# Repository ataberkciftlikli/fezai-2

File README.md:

# fezai-2
Halley'in Çırakları Rocket Team - Fezai II - Flight Computer - 2021

Main Flight Computer -> Teensy 3.5 Microcontroller
                     -> Adafruit Ultimate GPS
                     -> Xbee Pro S2C
                     -> BMP 280
                     -> MPU6050
                     -> LM2596-ADJ
                     -> IRF540

Second Flight Computer -> Teensy 3.5 Microcontroller
                       -> Adafruit Ultimate GPS
                       -> Xbee Pro S2C
                       -> BMP 180
                       -> MPU9050
                       -> LM2596-ADJ
                       -> IRF540

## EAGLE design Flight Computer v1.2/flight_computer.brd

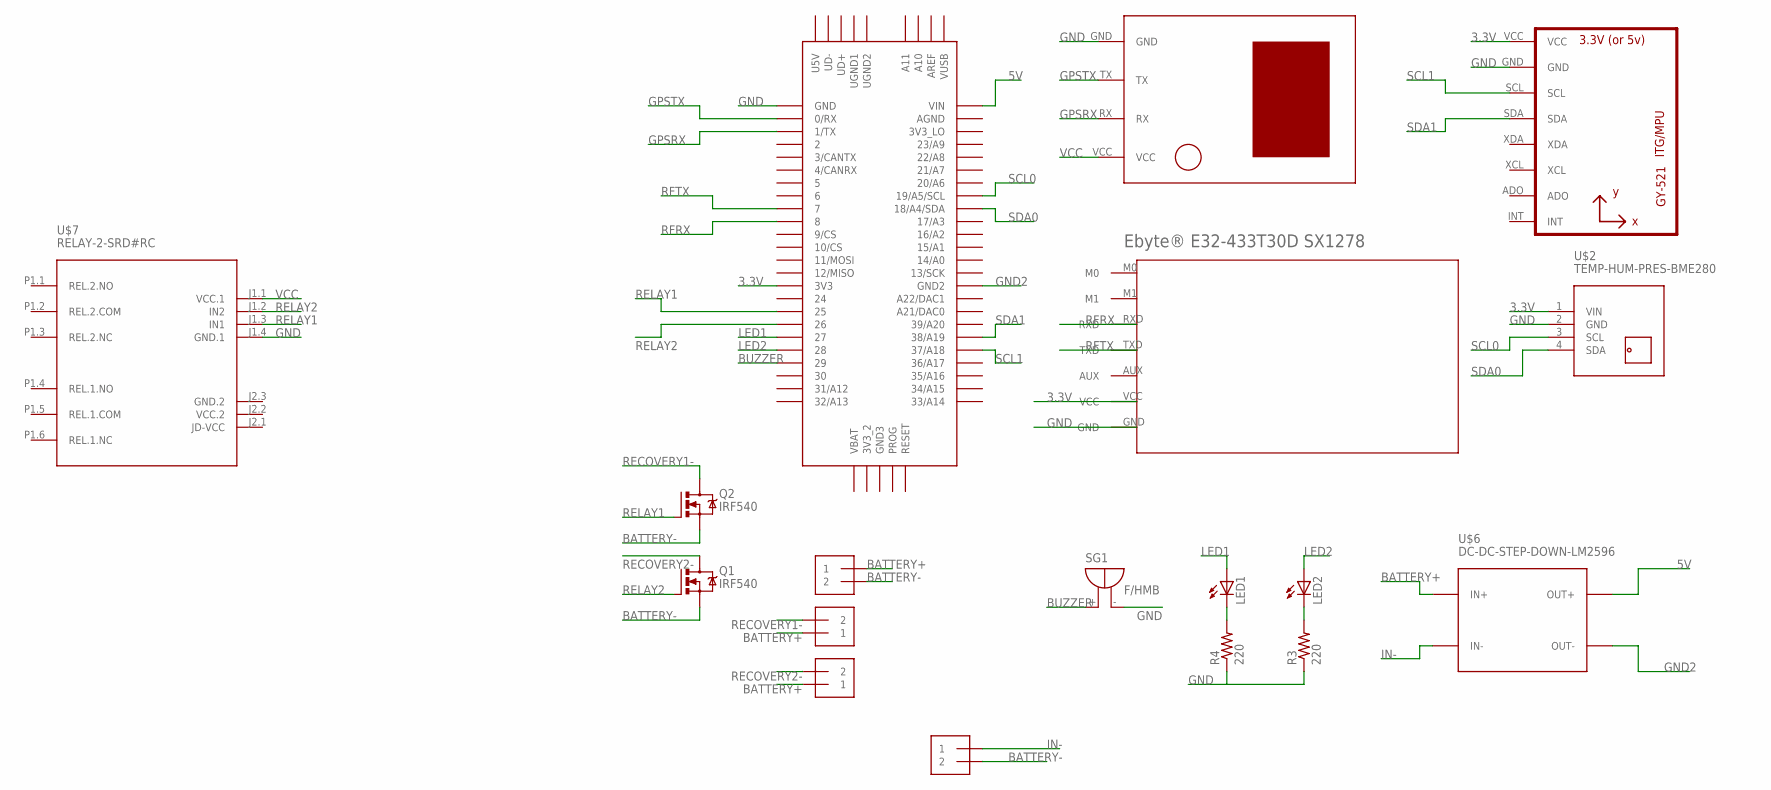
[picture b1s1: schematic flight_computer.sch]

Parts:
J1, J2, J3, J4: 1X2-3.5MM
LED1, LED2: LED5MM
Q1, Q2: IRF540; TO220BV
R3, R4: 220; 0204/7
SG1: F/HMB
U1: GY-521MPU6050; GY-521
U$1: U-BLOX-NEO6V2
U$2: TEMP-HUM-PRES-BME280
U$3: TEENSY_3.5/3.6
U$4: EBYTE®E32-433T30DSX1278; E32-433T30D
U$6: DC-DC-STEP-DOWN-LM2596
U$7: RELAY-2-SRD#RC

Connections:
3.3V: U1.VCC, U$2.1 (VIN), U$3.3V3, U$4.VCC
5V: U$3.VIN, U$6.OUT+
BATTERY+: J1.1, J2.1, J3.1, U$6.IN+
BATTERY-: J1.2, J4.2, Q1.S, Q2.S
BUZZER: SG1.+, U$3.29
GND: R3.1, R4.1, SG1.-, U1.GND, U$1.GND, U$2.2 (GND), U$3.GND, U$4.GND, U$7.J1.4 (GND.1)
GND2: U$3.GND2, U$6.OUT-
GND.2: U$7.J2.3 (GND.2)
GPSRX: U$1.RX, U$3.1/TX
GPSTX: U$1.TX, U$3.0/RX
IN-: J4.1, U$6.IN-
LED1: LED1.A, U$3.27
LED2: LED2.A, U$3.28
unnamed: LED1.K (C), R4.2
unnamed: LED2.K (C), R3.2
RECOVERY1-: J2.2, Q2.D
RECOVERY2-: J3.2, Q1.D
RELAY1: Q2.G, U$3.25, U$7.J1.3 (IN1)
RELAY2: Q1.G, U$3.26, U$7.J1.2 (IN2)
RFRX: U$3.8, U$4.RXD
RFTX: U$3.7, U$4.TXD
SCL0: U$2.3 (SCL), U$3.19/A5/SCL
SCL1: U1.SCL, U$3.37/A18
SDA0: U$2.4 (SDA), U$3.18/A4/SDA
SDA1: U1.SDA, U$3.38/A19
VCC: U$1.VCC, U$7.J1.1 (VCC.1)
VCC.2: U$7.J2.2 (VCC.2)

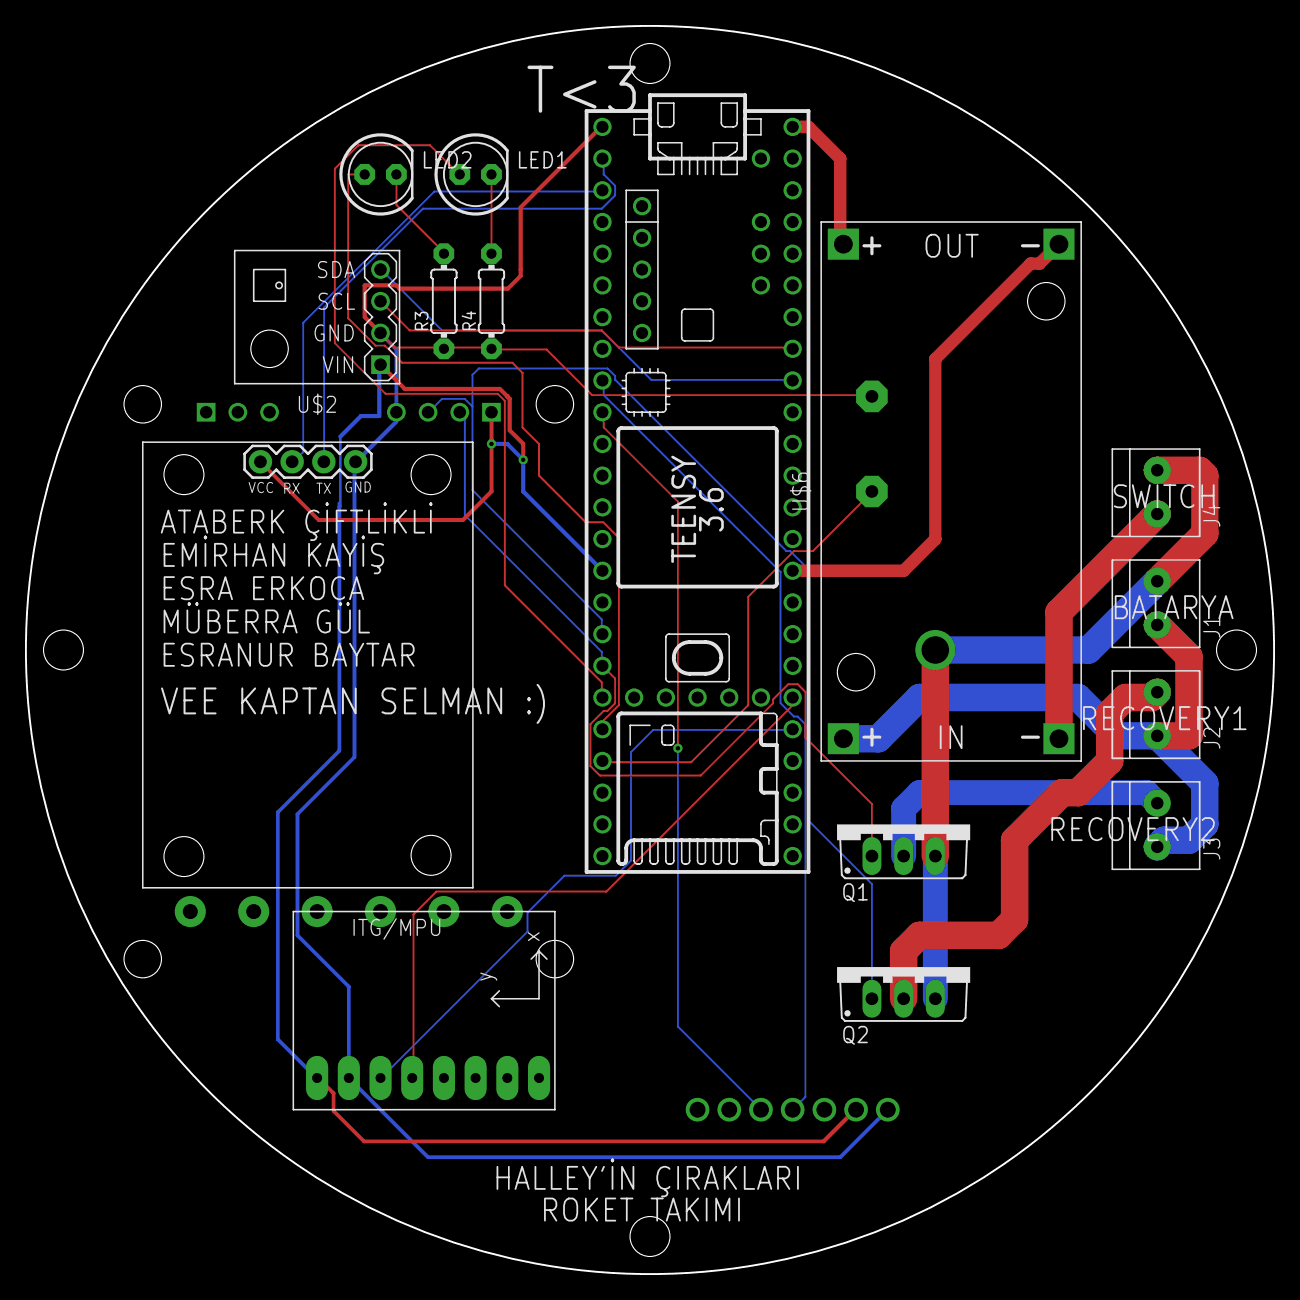
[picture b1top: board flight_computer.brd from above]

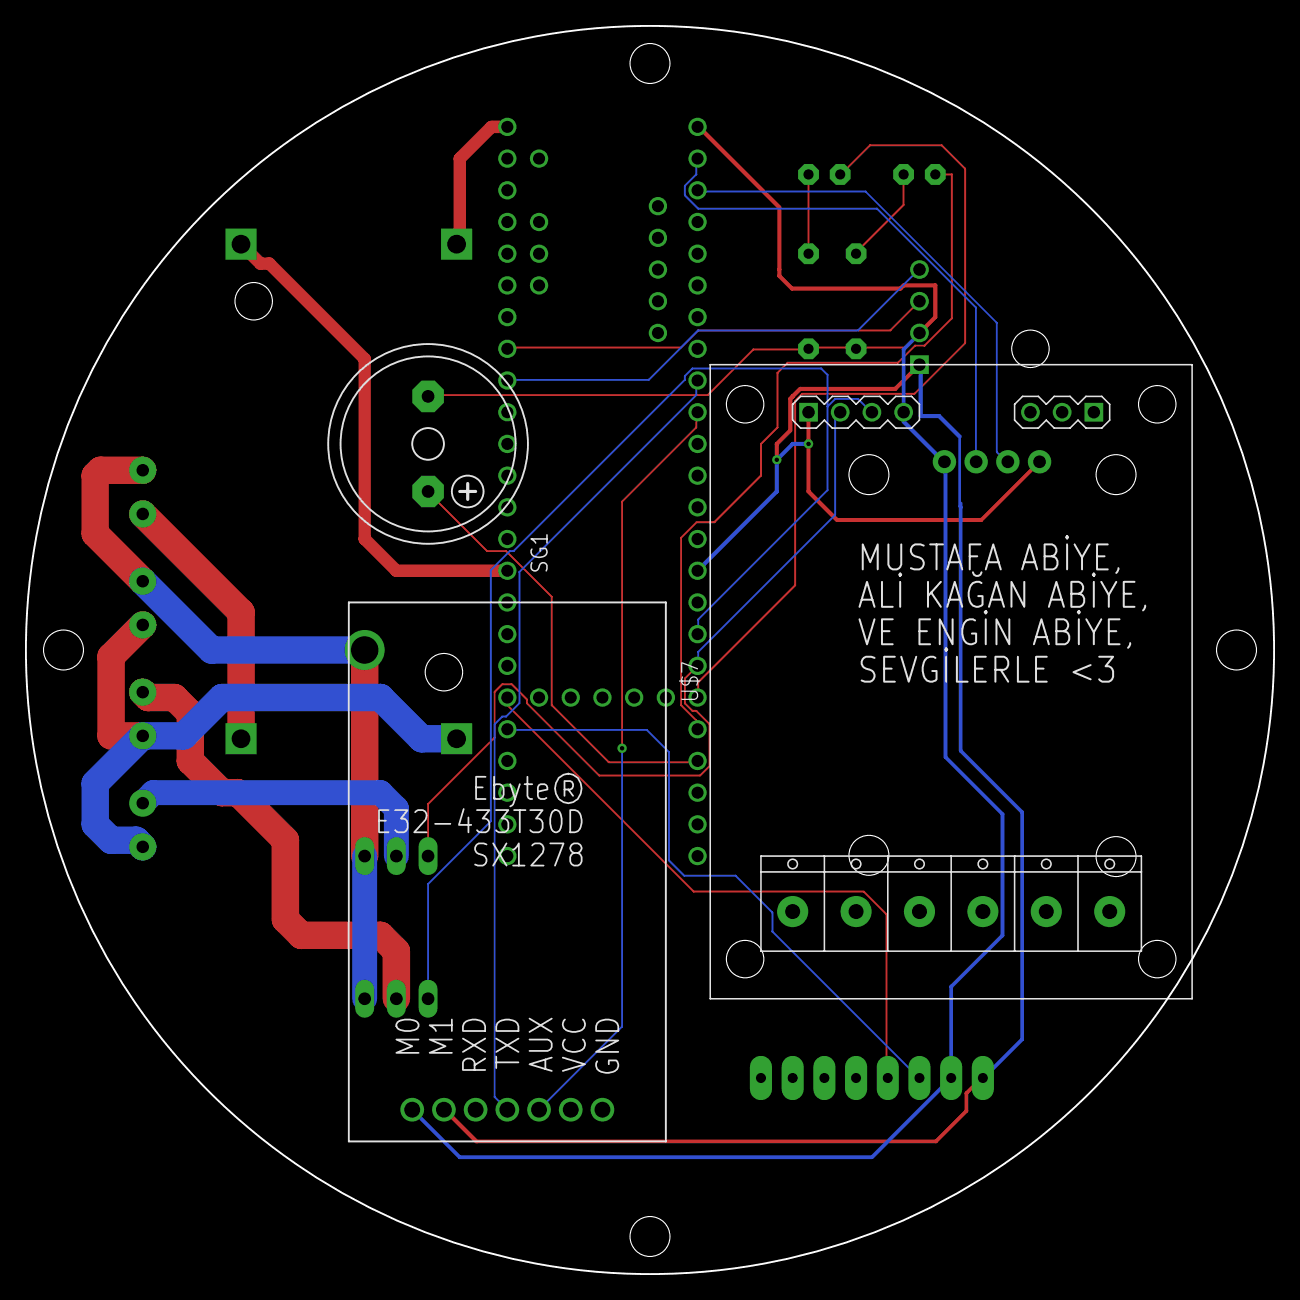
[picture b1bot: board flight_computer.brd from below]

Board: 2 copper layers, 100.0 x 100.0 mm, 18 parts (3 on the bottom side), 25 nets.

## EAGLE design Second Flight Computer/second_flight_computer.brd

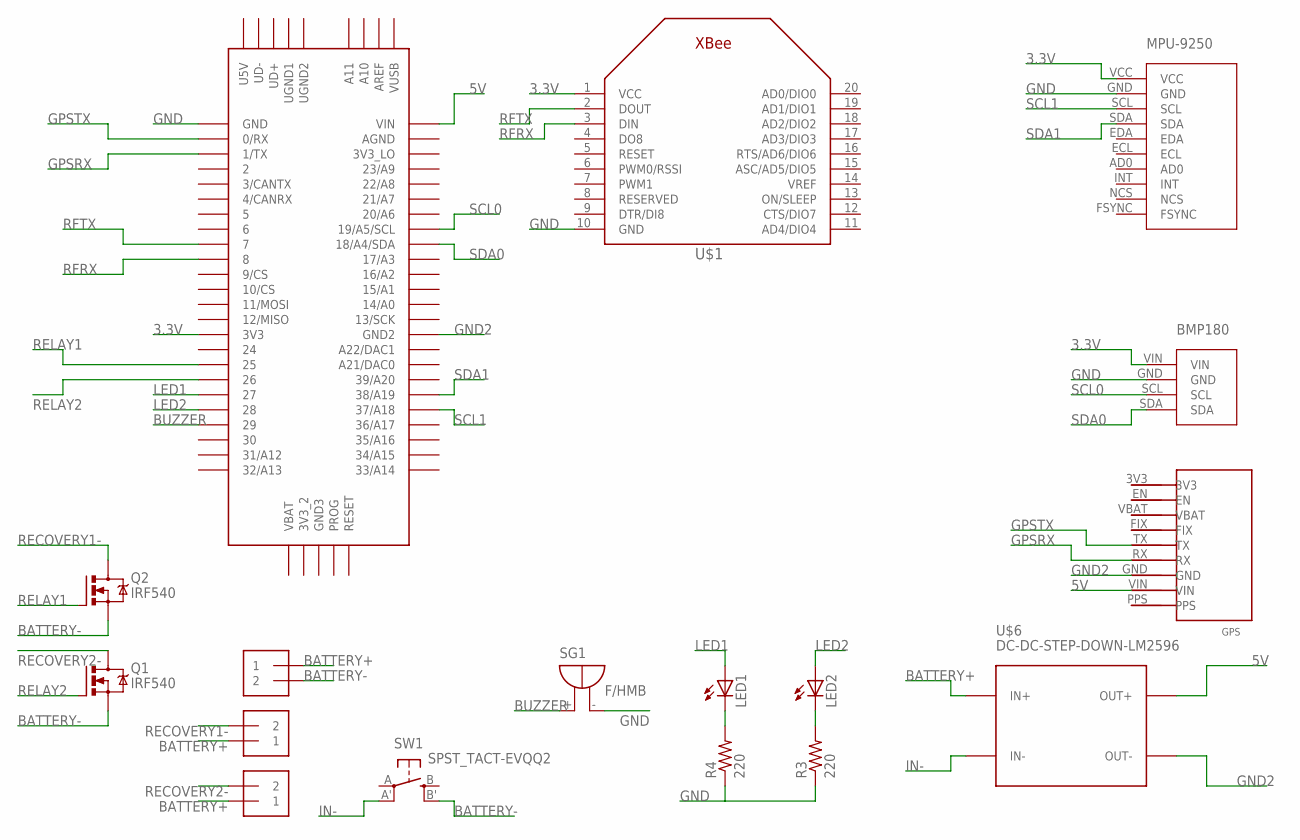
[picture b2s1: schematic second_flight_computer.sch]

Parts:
BMP1: BMP180
J1, J2, J3: 1X2-3.5MM
LED1, LED2: LED5MM
MPU-1: MPU-9250
Q1, Q2: IRF540; TO220BV
R3, R4: 220; 0204/7
SG1: F/HMB
SW1: SPST_TACT-EVQQ2; EVQ-Q2
U$1: XBEE
U$3: TEENSY_3.5/3.6
U$5: GPS
U$6: DC-DC-STEP-DOWN-LM2596

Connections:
3.3V: BMP1.VIN, MPU-1.VCC, U$1.1 (VCC), U$3.3V3
5V: U$3.VIN, U$5.VIN, U$6.OUT+
BATTERY+: J1.1, J2.1, J3.1, U$6.IN+
BATTERY-: J1.2, Q1.S, Q2.S, SW1.B' (S1)
BUZZER: SG1.+, U$3.29
GND: BMP1.GND, MPU-1.GND, R3.1, R4.1, SG1.-, U$1.10 (GND), U$3.GND
GND2: U$3.GND2, U$5.GND, U$6.OUT-
GPSRX: U$3.1/TX, U$5.RX
GPSTX: U$3.0/RX, U$5.TX
IN-: SW1.A' (P1), U$6.IN-
LED1: LED1.A, U$3.27
LED2: LED2.A, U$3.28
unnamed: LED1.K (C), R4.2
unnamed: LED2.K (C), R3.2
RECOVERY1-: J2.2, Q2.D
RECOVERY2-: J3.2, Q1.D
RELAY1: Q2.G, U$3.25
RELAY2: Q1.G, U$3.26
RFRX: U$1.3 (DIN), U$3.8
RFTX: U$1.2 (DOUT), U$3.7
SCL0: BMP1.SCL, U$3.19/A5/SCL
SCL1: MPU-1.SCL, U$3.37/A18
SDA0: BMP1.SDA, U$3.18/A4/SDA
SDA1: MPU-1.SDA, U$3.38/A19

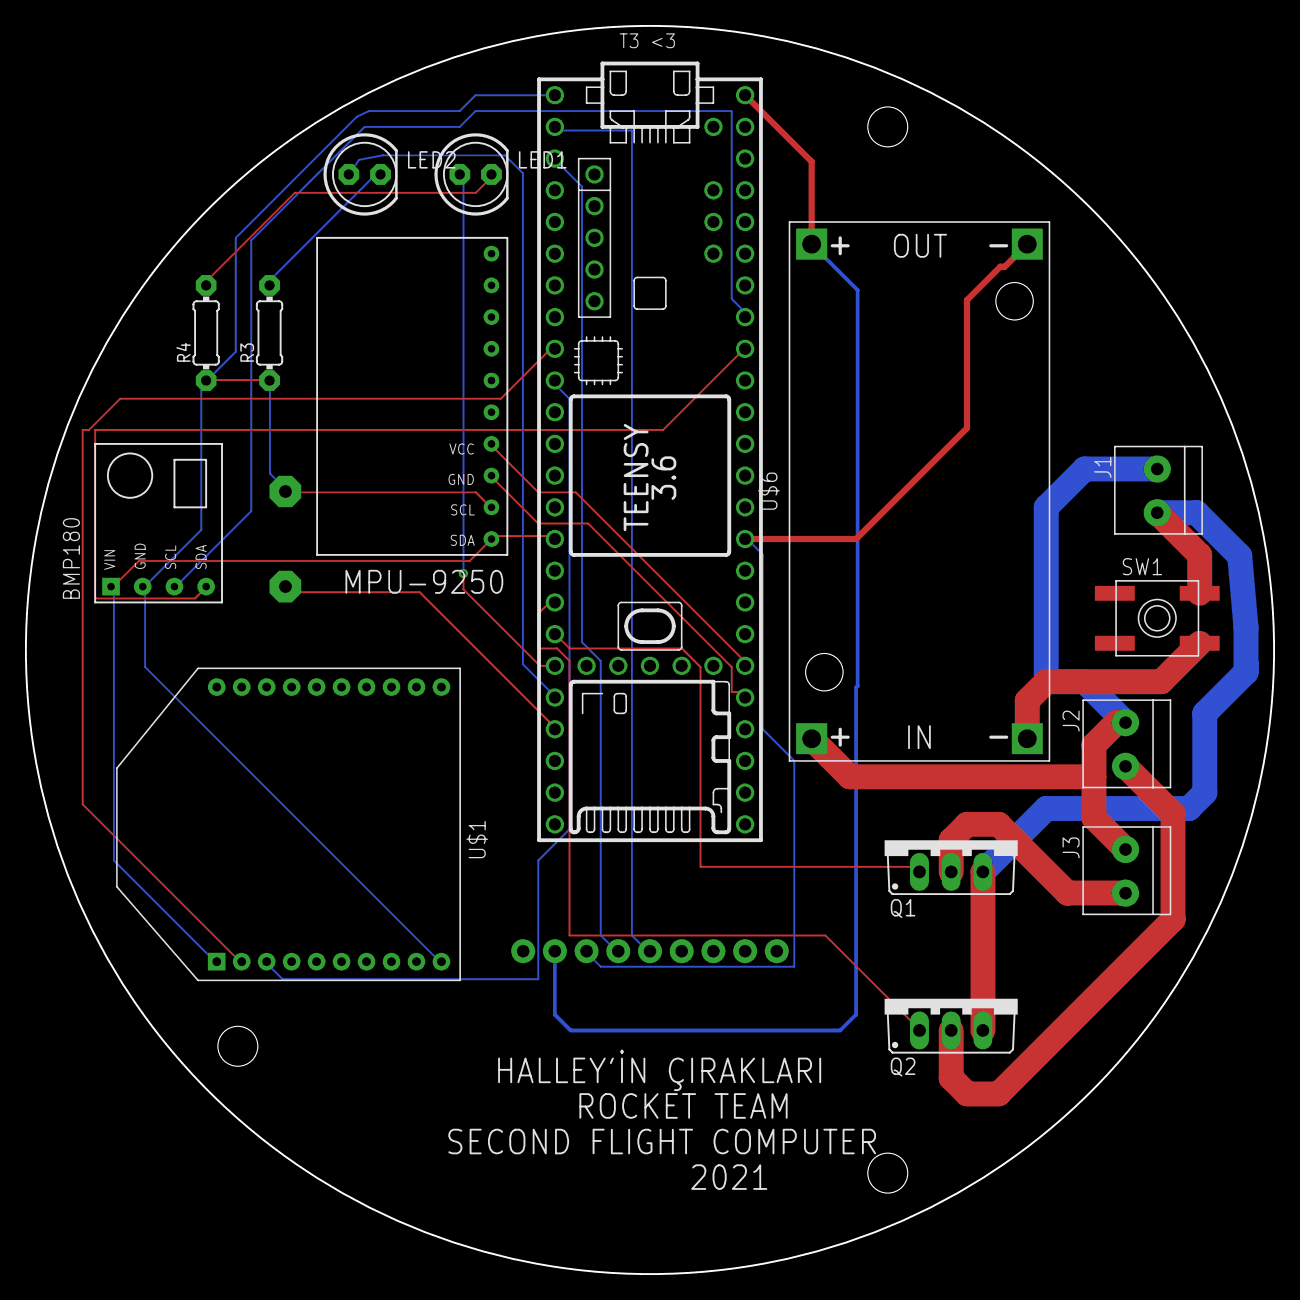
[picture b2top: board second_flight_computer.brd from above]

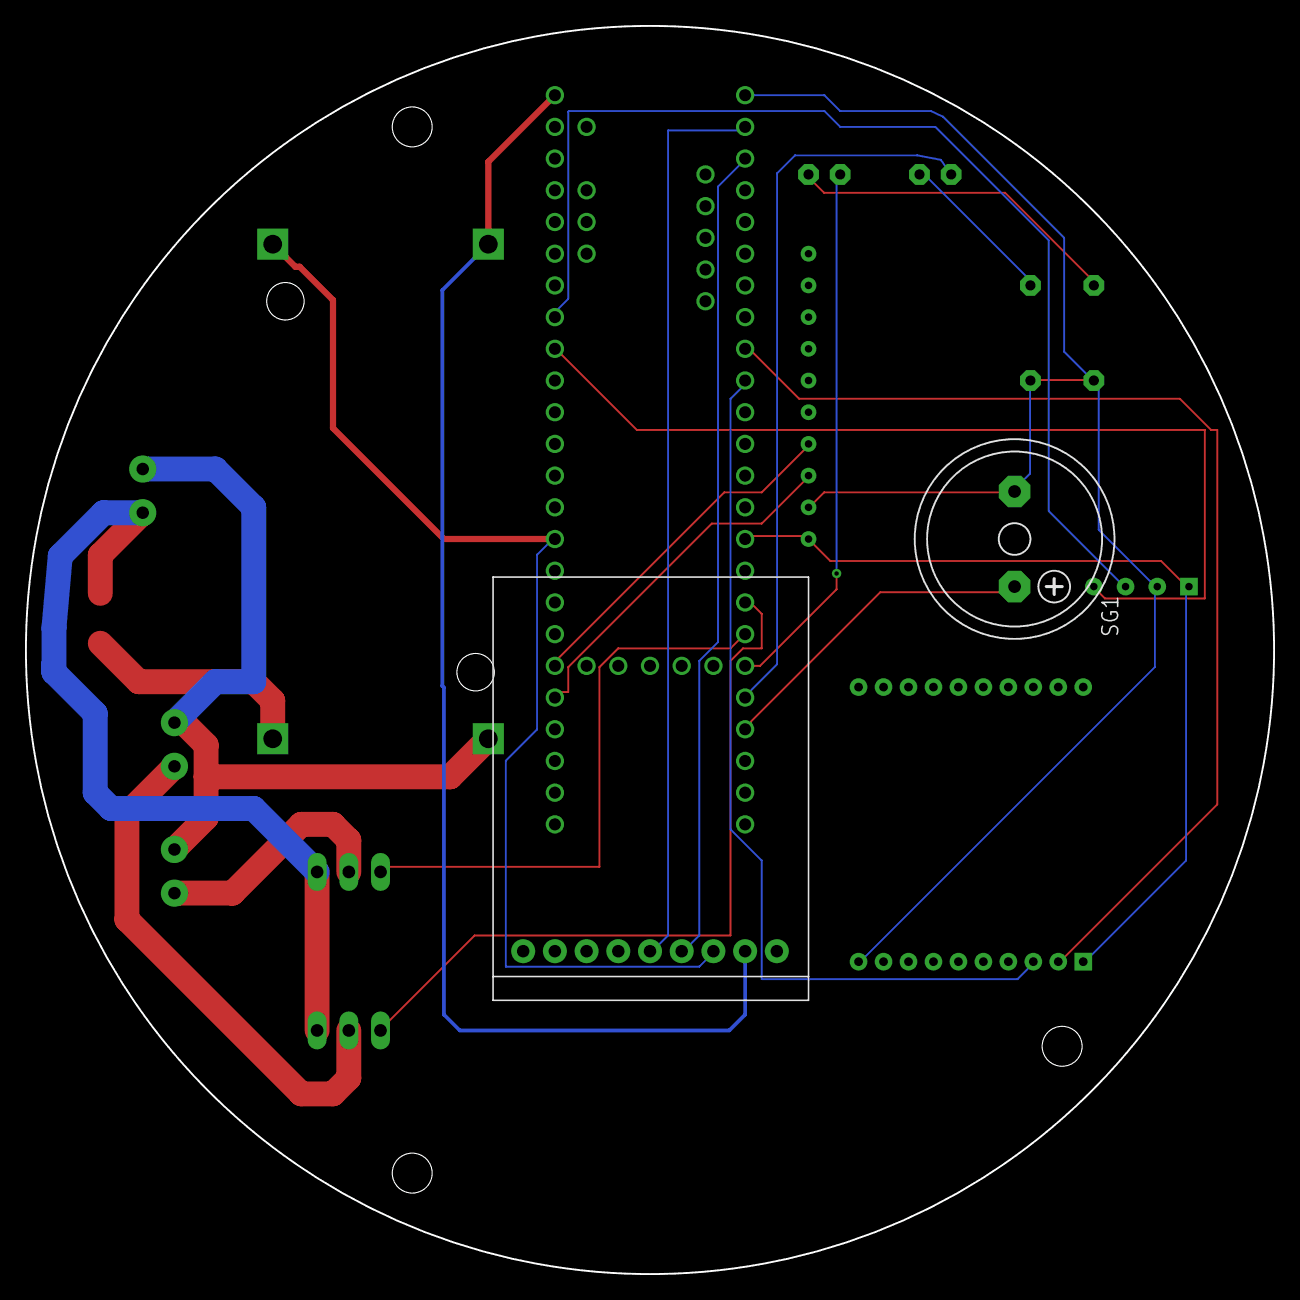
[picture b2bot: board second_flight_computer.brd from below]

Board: 2 copper layers, 100.0 x 100.0 mm, 17 parts (2 on the bottom side), 24 nets.

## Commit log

2021-03-02 Main Flight Computer PCB Design
2021-03-03 Second Flight Computer
2021-03-03 Second Flight Computer PCB Design Updated

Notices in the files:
parts and their libraries:
diy-modules: Released under the Creative Commons Attribution 4.0 International License: http://creativecommons.org/licenses/by/4.0
